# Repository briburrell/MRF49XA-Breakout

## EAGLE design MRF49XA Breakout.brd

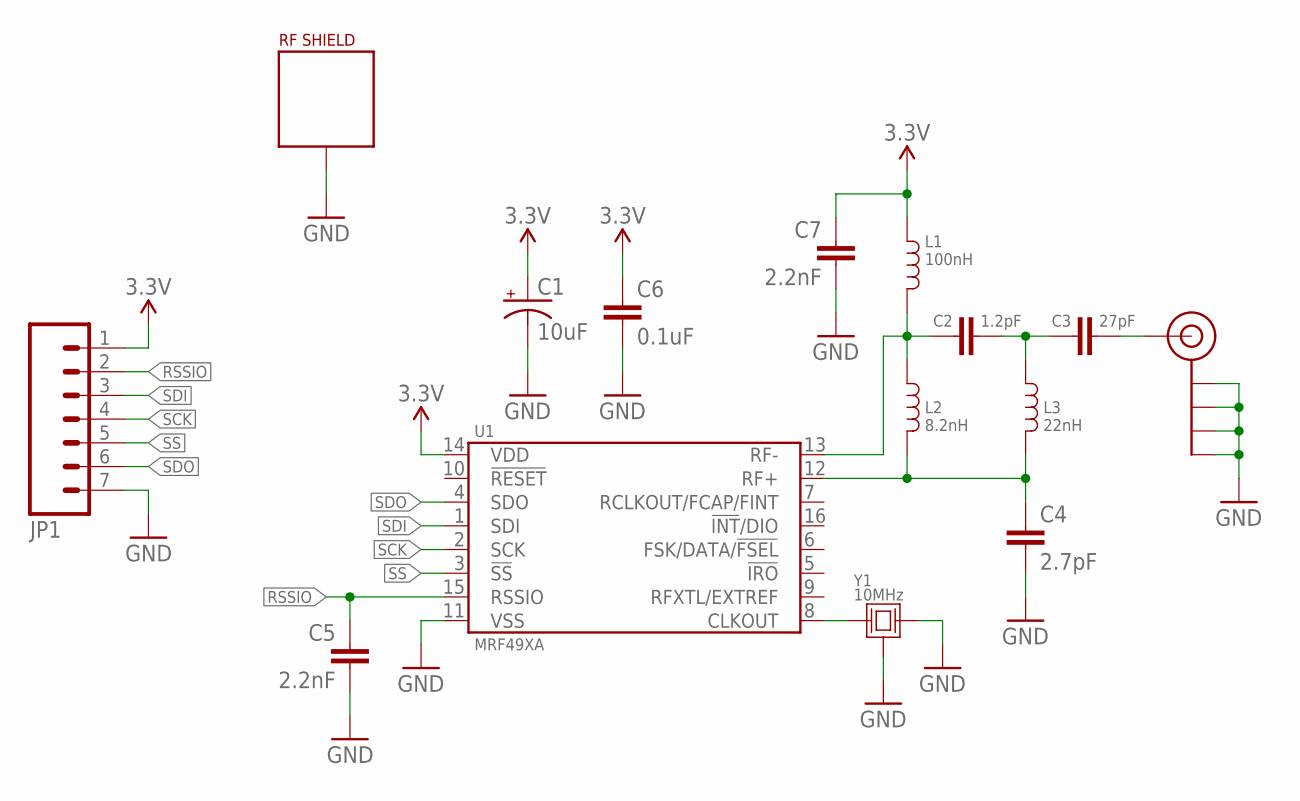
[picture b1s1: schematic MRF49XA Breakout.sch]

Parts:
C1: 10uF; 0805-CAP_POL
C2: 1.2pF; 0805
C3: 27pF; 0805
C4: 2.7pF; 0805
C5, C7: 2.2nF; 0805
C6: 0.1uF; 0805
J$1: SMA_EDGE; SMA-EDGE
JP1: M07; 1X07
L1: 100nH; 0805
L2: 8.2nH; 0805
L3: 22nH; 0805
U1: MRF49XA; TSSOP-16
U$1: RF-SHIELD; RF_SHIELD-.65X.65
Y1: 10MHz; FA-238

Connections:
3.3V: C1.A (+), C6.1, C7.1, JP1.1, L1.1, U1.14 (VDD)
GND: C1.C (-), C4.2, C5.2, C6.2, C7.2, J$1.GND@0 (GND), J$1.GND@1 (GND), J$1.GND@2 (GND), J$1.GND@3 (GND), JP1.7, U1.11 (VSS), U$1.P$1, U$1.P$2, U$1.P$3, U$1.P$4, U$1.P$5, U$1.P$6, U$1.P$7, U$1.P$8, U$1.P$9, U$1.P$10, U$1.P$11, U$1.P$12, Y1.2 (GND), Y1.3 (2), Y1.4 (GND)
unnamed: C4.1, L2.2, L3.2, U1.12 (RF+)
unnamed: C2.1, L1.2, L2.1, U1.13 (RF-)
unnamed: C2.2, C3.1, L3.1
unnamed: C3.2, J$1.SIG (SIGNAL)
unnamed: U1.8 (CLKOUT), Y1.1
RSSIO: C5.1, JP1.2, U1.15 (RSSIO)
SCK: JP1.4, U1.2 (SCK)
SDI: JP1.3, U1.1 (SDI)
SDO: JP1.6, U1.4 (SDO)
SS: JP1.5, U1.3 (!SS)

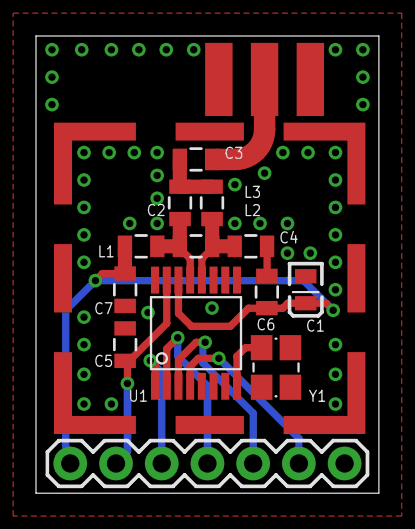
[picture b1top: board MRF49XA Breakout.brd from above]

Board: 2 copper layers, 19.1 x 25.4 mm, 15 parts (0 on the bottom side), 12 nets.

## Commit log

2016-08-12 Create LICENSE
2016-08-12 Added pdf documents

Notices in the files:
parts and their libraries:
SparkFun-Passives: Licensing: CC v3.0 Share-Alike You are welcome to use this library for commercial purposes.
